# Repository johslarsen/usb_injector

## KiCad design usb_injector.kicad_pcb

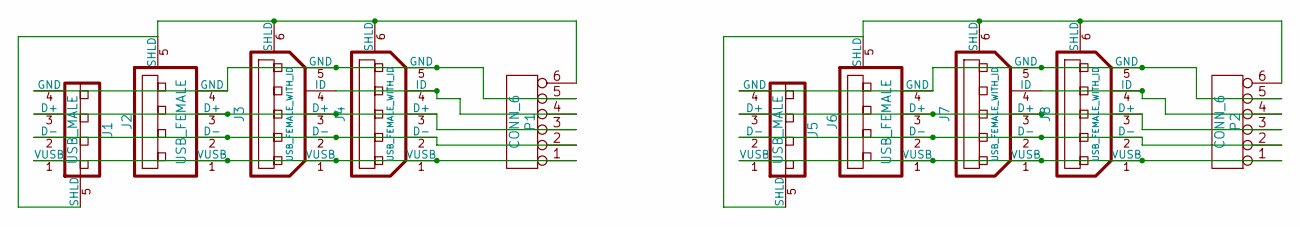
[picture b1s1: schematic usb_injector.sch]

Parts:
J1, J5: USB_MALE
J2, J6: USB_FEMALE
J3, J4, J7, J8: USB_FEMALE_WITH_ID
P1, P2: CONN_6

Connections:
unnamed: J1.1 (VUSB), J2.1 (VUSB), J3.1 (VUSB), J4.1 (VUSB), P1.1
unnamed: J1.2 (D-), J2.2 (D-), J3.2 (D-), J4.2 (D-), P1.2
unnamed: J1.3 (D+), J2.3 (D+), J3.3 (D+), J4.3 (D+), P1.3
unnamed: J1.4 (GND), J2.4 (GND), J3.5 (GND), J4.5 (GND), P1.5
unnamed: J1.5 (SHLD), J2.5 (SHLD), J3.6 (SHLD), J4.6 (SHLD), P1.6
unnamed: J3.4 (ID), J4.4 (ID), P1.4
unnamed: J5.1 (VUSB), J6.1 (VUSB), J7.1 (VUSB), J8.1 (VUSB), P2.1
unnamed: J5.2 (D-), J6.2 (D-), J7.2 (D-), J8.2 (D-), P2.2
unnamed: J5.3 (D+), J6.3 (D+), J7.3 (D+), J8.3 (D+), P2.3
unnamed: J5.4 (GND), J6.4 (GND), J7.5 (GND), J8.5 (GND), P2.5
unnamed: J5.5 (SHLD), J6.5 (SHLD), J7.6 (SHLD), J8.6 (SHLD), P2.6
unnamed: J7.4 (ID), J8.4 (ID), P2.4

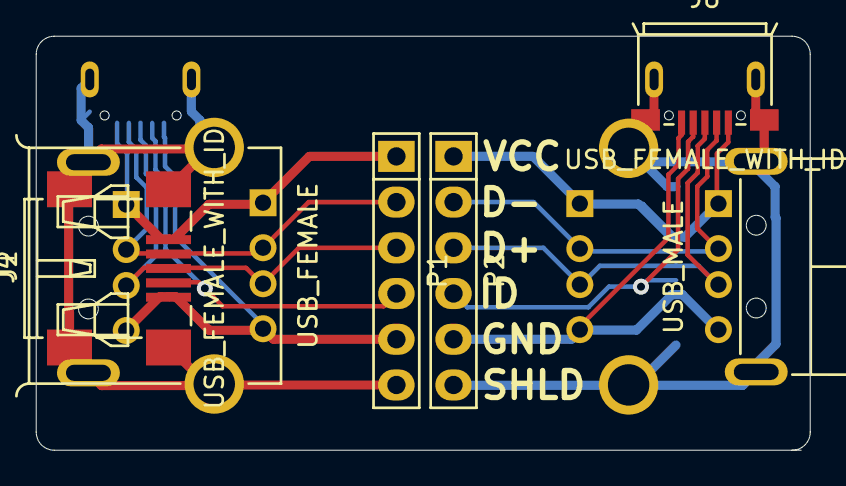
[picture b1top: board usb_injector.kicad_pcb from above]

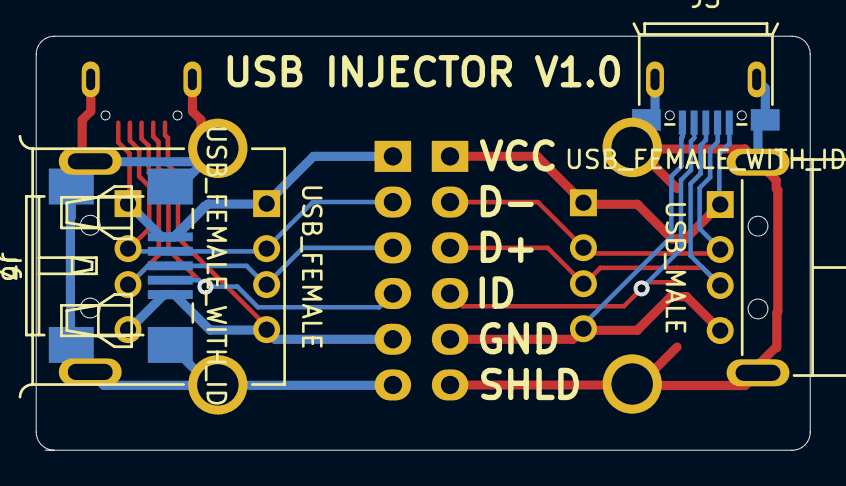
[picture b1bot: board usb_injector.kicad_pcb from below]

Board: 2 copper layers, 43.0 x 23.0 mm, 10 parts (4 on the bottom side), 12 nets.

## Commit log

2015-01-09 added CC-0 license
2015-01-09 added lib/Connectors.pretty submodule
2015-01-09 completed revision 1
2015-01-11 switched to UNLICENSE
2015-01-11 changed footprints to comply with KiCad Library Conventions and moved board/components so that the board aligns with a 5mm grid
2015-01-14 aligned board to 1mm and rounded corners
2015-01-14 changed to relative submodules
2015-02-07 added v1.0 output files
2015-02-08 updated components, fixed .1" headers spacing, rearranged header pinout such that full size USB-connectors have length-matched traces and moved USB-mini connector alongside USB-micro connector
